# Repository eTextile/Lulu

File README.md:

# Lulu-MCU

**Programming light into textile**

Lulu is a hardware solution that interfaces between an LED light source, an optic fiber strand or bundle and soft circuit connections.
Providing an optic fiber connection toolset and workflow for E-Textiles and Wearable Technology applications.

### About The project
Lulu is providing a simple, reliable toolset for people who want to use side glow optical fibers in their eTextile and wearable projects.
Use of light in textile and fashion design is becoming more and more common and many schools started to teach this subject as a part of their textile design curriculum.
Optic fibers could be embedded in textiles as embroidery, in weaving, knitting and knotting process and many textile designs have been realized in recent years.
But often the designers lack the toolset for connecting the light sources with the embedded optic fibers, resulting in re-purposing bulky connectors and technology and hiding them behind the textiles.
Currently, each designer has to come up with their own re-purposed or DIY solution.
Lulu is a connector that optimizes the efficiency of the connection between the light source and the optical fibers to get a strong illumination.
Instead of struggling to solve the light source and connection problem, the designer can concentrate on the aesthetic and textile making process issues.

### Lulu branches
- **Lulu-star (master)**
  - This branch provide a tiny PCB with a 200mA LED, PWM driver and an optic fiber connector.
- **Lulu-daisy**
  - This branch provide a tiny PCB with an addressable LED (WS2812-mini, Dotstar, etc) and an optic fiber connector.
- **Lulu-MCU**
  - This branch provide a tiny PCB with a built in MCU (ATTiny10) that allow one-wire communication bus system.
- **Lulu**
  - This branch provide a motherboard (Lucette) that drive up to 16 Lulu that only contain a power LED and an optic fiber connector.

### Development tools & DOCs
 * **Web page**: [http://lulu.eTextile.org](http://lulu.eTextile.org "The project Web page")
 * **Kobakant web page**: [http://www.kobakant.at/KOBA/lulu-developments](http://www.kobakant.at/KOBA/lulu-developments "Kobakant project Web page")
 * **Repository**: [https://github.com/eTextile/Lulu/tree/master](https://github.com/eTextile/Lulu/tree/master "The project repository")
 * **License**: [CC-BY-SA](https://github.com/eTextile/Lulu/blob/master/LICENSE "See the Lulu license project")
 * **Video**: [Lulu project by Hannah](https://www.youtube.com/watch?v=drAoLd_eUWk "Lulu project Introduction")
 * **Video**: [Lulu project by Maurin](https://vimeo.com/249171264 "eTextile bus solution")
 * **Mail**: [lulu@etextile.org](mailto:lulu@etextile.org "eMail us")
 * **IRC**: [Riot](https://vector.im/develop/#/room/#lulu:matrix.org "Join us on the chat to collaborate in the development")
 * **Pictures**: [Flickr](https://www.flickr.com/groups/3908991@N25/ "Share your Lulu pictures project")

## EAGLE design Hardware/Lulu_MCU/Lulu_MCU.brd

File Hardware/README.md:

# Lulu-MCU / Hardware
**Programming light into textile**

# Lulu-MCU

## Hardware design
This branch of the Lulu project is using a 200mA power LED with current current circuitry.
As the project is focussing on embedded electronics we chosed an high power LED ; OSRAM OSLON SX seeking 200 mA/h 
Then it can be 5 hour of autonomy with a 1000 mA Lypo battery.
The LED is also providing a narrow angle (60°) this helps to focus the light in to the optic fiber wafer.
    See datasheet: https://github.com/eTextile/Lulu/blob/master/Hardware/DOCs/LY_CN5M.pdf
The brass tube connector have been selected to fit the outer diameter of the LED optics.
The PCB triangle shape have been selected to fit the zero waste production process.
All the components are SMD package to reduce the size and price of th PCB.
We have been experiencing a new way to hand solder the LED on the edge of the PCB but it is still not so handy.
Custom tooling will be designed and tested to help in that soldering process.

## Release notes
### Lulu-MCU 4.0.0
- Initial release (forked from Lulu-star 2.1.3)

## Lulu-MCU connecting
- [VCC] (+) 3.3 to 5 Voltes
- [GND] (-) GND
- [DATA] oneWire data bus

        +---+--------------+-------------------+-----
        |   |              |                   |
    + __|__ |              |                   |
    -  ___  |              |                   |
        |   |              |                   |
        +---|--------------|--+----------------|--+--
        |   |              |  |                |  |
        |   |            __|__|__            __|__|__
       _|___|_           \ +  - /            \ +  - /
      | +   - |           \    /              \    /
      |   M   |            \  /                \  /
      |   C   |             \/                  \/
      |   U   |              |                   |
      |       |--------------------- DATA ------------
      |_______|

## Lulu-MCU Powering
The Lulu-MCU board must be powered with a voltage betwin 3.3V to 5V.
DO NOT USE 3V single coin battery - voltage is too low and it will not work for long.
Prefer the use of rechargeable Lipo battery with small Lipo charger.
- https://www.powerstream.com/thin-primary-lithium.htm
- Charger technology
- Low discharge protection

## Lulu-MCU built-in LED driver
### Constant current source circuitry

**References**
- https://learn.adafruit.com/pixie-3-watt-smart-chainable-led-pixels/design
- http://www.instructables.com/id/Power-LED-s---simplest-light-with-constant-current/
- https://scienceprog.com/building-simple-constant-current-power-led-driver/
- http://www.pcbheaven.com/userpages/LED_driving_and_controlling_methods/?topic=worklog&p=3

### Circuit part list
| Designator                                      | MPN                       | Package                | Price per unit | Weblink                |
| ----------------------------------------------- | ------------------------- | -----------------------|--------------- |------------------------|
| Power LED / OSRAM 200mA                         | LY CN5M                   |                        | 0.65 $         | [LY-CN5M](https://fr.aliexpress.com/item/OSRAM-OSLON-SX-High-Power-LED-0-5W-3030-Yellow-LY-CN5M/32865040281.html?spm=a2g0s.9042311.0.0.27426c371XVtDl) |
| Q1 - large N-channel MOSFET                     | IRLML2060TRPBF            | SOT-23                 | 0,126 €        | [IRLML2060TRPBF](https://www.digikey.com/product-detail/en/infineon-technologies/IRLML2060TRPBF/IRLML2060TRPBFCT-ND/2271917) |
| T1 - small NPN transistor                       | MMBT2222A                 | SOT-23                 | 0,0412 €       | [MMBT2222A](https://www.digikey.com/product-detail/en/diodes-incorporated/MMBT2222A-7-F/MMBT2222A-FDICT-ND/815723) |
| R1 - 47k-ohm resistor                           | RT0603DRD0747KL           | 0603                   | 0,0147 €       | [R-47k-ohm ](https://www.digikey.com/product-detail/en/yageo/RT0603DRD0747KL/311-47KDCT-ND/1035828) |
| R2 - current set resistor - 2.7 ohms 1/4 watt   |                           | 1206                   | 0,0246 €       | [R-2.7-ohm](https://fr.farnell.com/walsin/wr12w2r70ftl/resist-couche-epaisse-2-7r-1-0/dp/2668305) |
| R3 - 10k pull-down resistor                     | RT0603DRD0710KL           | 0603                   | 0,     €       | [R-10k-ohm](https://www.digikey.com/product-detail/en/yageo/RT0603DRD0710KL/311-10KDCT-ND/1035680) |
| ATTiny10                                        |                           | SOT-                   | 0,     €       | [ATTiny10](...) |

**R2** is used to set the current limit and this doesn't depends on the voltage supply VDD.
**Q1** is used as a variable resistor. **Q1** starts out turned on by **R1**.
**T1** is used as an over-current sensing switch, and **R2** is the "sense resistor" that triggers **T1** when too much current is flowing.
The main current flow is through the LED's, through **Q1**, and through **R2**.
When too much current flows through **R2**, **T1** will start to turn on, which starts turning off **Q1**. Turning off **Q1** reduces the current through the LED's and **R2**.
So we've created a **feedback loop**, which continuously tracks the current and keeps it exactly at the set point at all times.
The NPN transistors **T1** have a specified 0.6V drop between base and emitter when on.
This means the voltage across their respective shunt resistors **R2** will always be 0.6V.
According to Ohm’s law, this means that the current through them will be '0.6 V / 2.7 Ohm', or about 222mA.

## PCB manufacturing characteristics
  - Base Material : FR-4 TG13
  - No. of Layers : 2 layers
  - PCB Thickness : 1 mm
  - PCB Color : Yelow
  - Surface Finish : HASL
  - Minimum Solder Mask Dam : 0.4 mm
  - Copper Weight : 1oz (35 µm)
    - For 300 mA we nead 0.15mm copper traces (https://www.4pcb.com/trace-width-calculator.html)
  - Minimum Drill Hole Size : 0.3 mm
  - Trace Width / Spacing : 5/5 mil
  - Blind or Buried Vias : NO
  - Plated Half-holes / Castellated Holes : YES
  - Impedance Control : NO

### Extra Part list
| Part                       | REF                      | Price per unit   | Weblink        |
| -------------------------- | ------------------------ | -----------------|--------------- |
| Brass tube                 | 2 mm Hole 5-10 mm Length |                  |                |
| JTE connector              | 1.5 / 8 mm               |                  |                |
| Optical fibres PMMA        | 0.25 mm x 35 pce         |                  |                |
| Optical fibres TPU         | 1.5, 2, 3 mm             |                  |                |
| Optical fibres tube + core |                          |                  | [www.leds-and-more.de](https://www.leds-and-more.de/catalog/15mm-lwl-lichtwellenleiter-lichtleiter-seitlich-leuchtend-p-1937.html?osCsid=2me5dl4q5amcvgb6tnbqfd87i5) |
| eTextile bus               |                          |                  |                |

## TODO
- [ ] Add ATTiny10 ont the KiCad desin
- [ ] Add POGO PINs on the PCB to flash the ATTiny10
- [ ] Change the PCB shape to put the tube angle to 90° from the e-Textile bus
- [ ] cool ref: https://hackaday.io/project/179554-tinyicoc

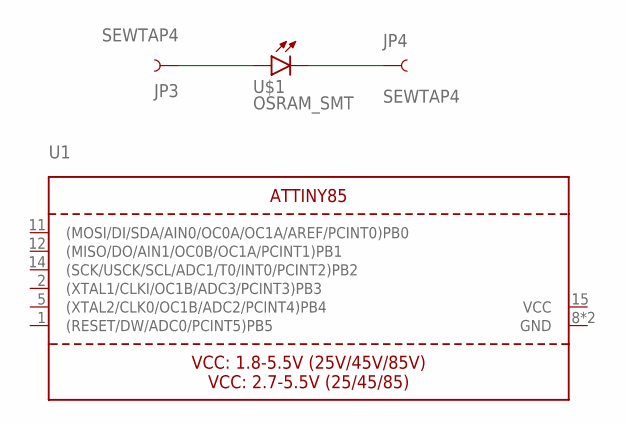
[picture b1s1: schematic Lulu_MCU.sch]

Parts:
JP3, JP4: SEWTAP4; PETAL-SMALL
U1: ATTINY85; MLF20_4X4MM_0.5MM_ATMEL
U$1: OSRAM_SMT; OSLON

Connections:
GND: U1.8 (GND), U1.THERMAL (GND)
unnamed: JP3.1, U$1.A
unnamed: JP4.1, U$1.C
VCC: U1.15 (VCC)

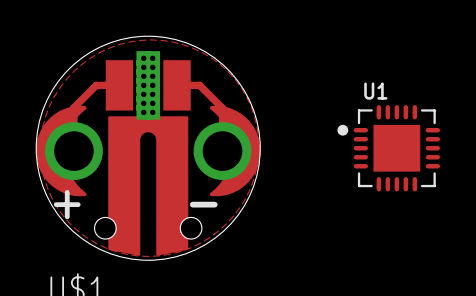
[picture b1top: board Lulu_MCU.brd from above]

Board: 2 copper layers, 12.4 x 12.4 mm, 4 parts (0 on the bottom side), 3 nets.

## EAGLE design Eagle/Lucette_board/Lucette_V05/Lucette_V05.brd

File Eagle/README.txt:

#Eagle

## Project content
 - Lucette Eagle PCB
 - Lulu Eagle PCB

See the README inside the project content files

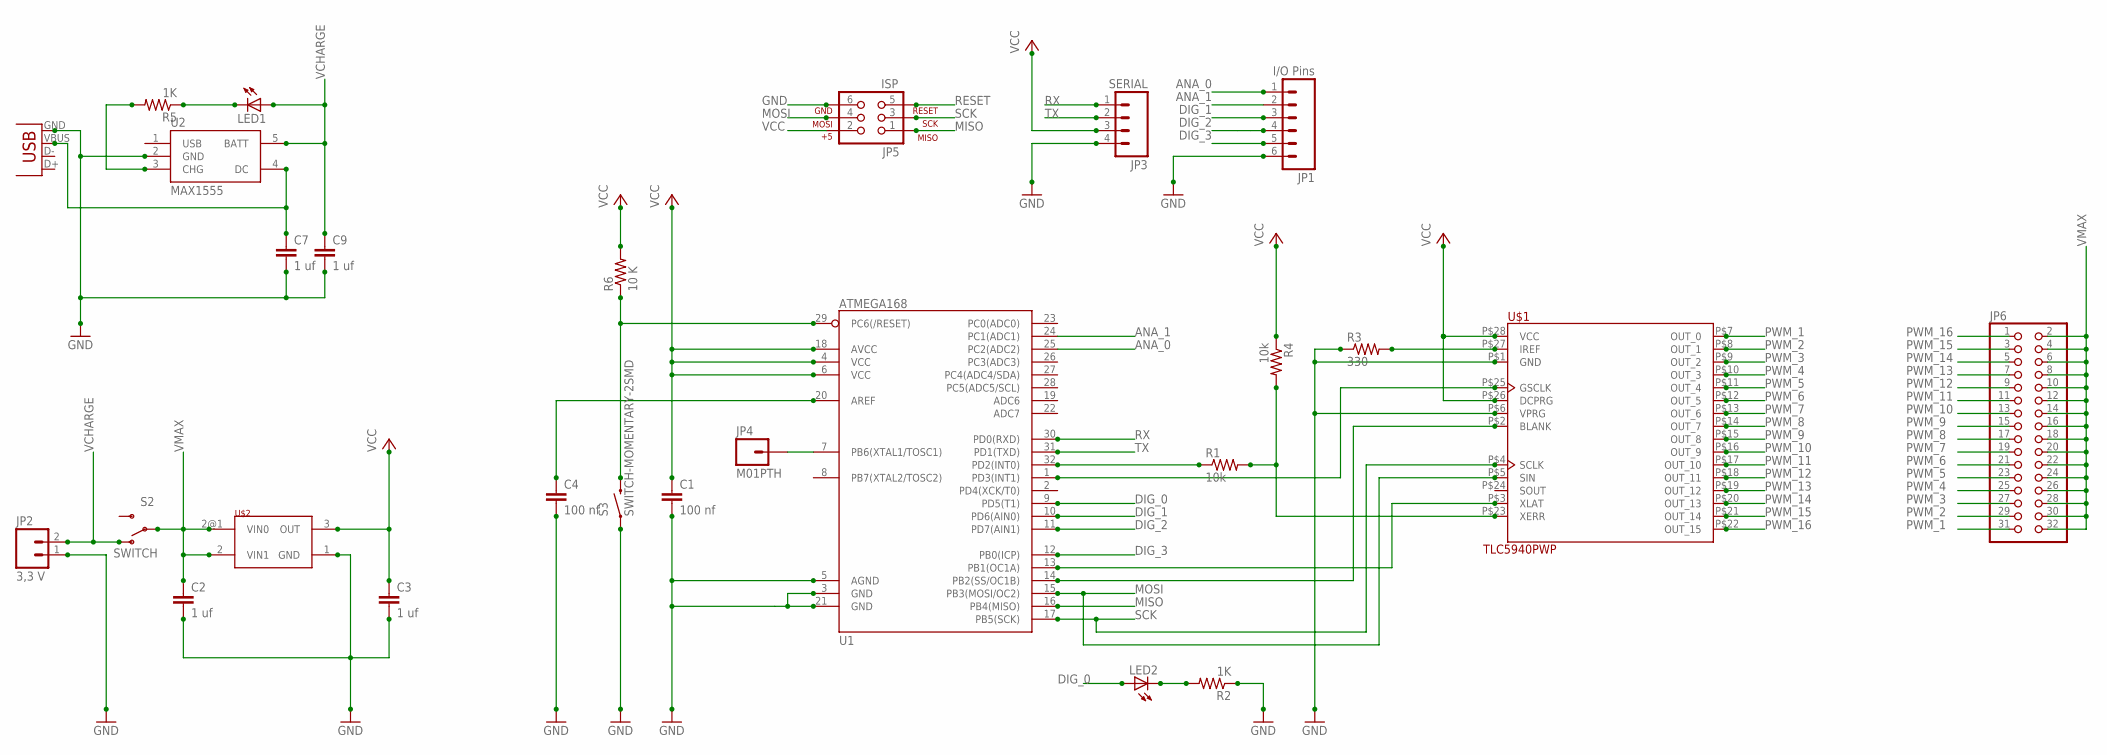
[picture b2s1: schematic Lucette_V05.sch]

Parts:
C1, C4: 100 nf; 0805
C2, C3, C7, C9: 1 uf; 0805
JP1: I/O Pins; 1X06-SMD
JP2: 3,3 V; S2B-PH
JP3: SERIAL; 1X04-SMD
JP4: M01PTH; 1X01
JP5: ISP; 2X3
JP6: PINHD-2X16/90; 2X16/90
LED1, LED2: LEDCHIP-LED0805; CHIP-LED0805
R1, R4: 10k; 1206
R2, R5: 1K; 1206
R3: 330; 1206
R6: 10 K; 1206
S2: SWITCH; AYZ0202
S3: SWITCH-MOMENTARY-2SMD; TACTILE_SWITCH_SMD
U1: ATMEGA168; TQFP32-08
U2: MAX1555; SOT23-5
U$1: TLC5940PWP; PWP-28
U$2: MCP1703; SOT98
X1: USBOLD; USB-MINIB-OLD

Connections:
ANA_0: JP1.1, U1.25 (PC2(ADC2))
ANA_1: JP1.2, U1.24 (PC1(ADC1))
DIG_0: LED2.A, U1.9 (PD5(T1))
DIG_1: JP1.3, U1.10 (PD6(AIN0))
DIG_2: JP1.4, U1.11 (PD7(AIN1))
DIG_3: JP1.5, U1.12 (PB0(ICP))
GND: C1.2, C2.2, C3.2, C4.2, C7.2, C9.2, JP1.6, JP2.1, JP3.4, JP5.6, R2.1, R3.1, S3.1, U1.3 (GND), U1.5 (AGND), U1.21 (GND), U2.2 (GND), U$1.P$1 (GND), U$1.P$6 (VPRG), U$2.1 (GND), X1.GND
MISO: JP5.1, U1.16 (PB4(MISO))
MOSI: JP5.4, U1.15 (PB3(MOSI/OC2)), U$1.P$5 (SIN)
unnamed: R1.2, R4.2, U$1.P$23 (XERR)
unnamed: R1.1, U1.32 (PD2(INT0))
unnamed: C7.1, U2.4 (DC), X1.VBUS
unnamed: R5.2, U2.3 (CHG)
unnamed: U1.13 (PB1(OC1A)), U$1.P$3 (XLAT)
unnamed: LED1.C, R5.1
unnamed: C4.1, U1.20 (AREF)
unnamed: R3.2, U$1.P$27 (IREF)
unnamed: JP4.1, U1.7 (PB6(XTAL1/TOSC1))
unnamed: LED2.C, R2.2
unnamed: U1.1 (PD3(INT1)), U$1.P$25 (GSCLK)
unnamed: U1.14 (PB2(SS/OC1B)), U$1.P$2 (BLANK)
PWM_1: JP6.31, U$1.P$7 (OUT_0)
PWM_2: JP6.29, U$1.P$8 (OUT_1)
PWM_3: JP6.27, U$1.P$9 (OUT_2)
PWM_4: JP6.25, U$1.P$10 (OUT_3)
PWM_5: JP6.23, U$1.P$11 (OUT_4)
PWM_6: JP6.21, U$1.P$12 (OUT_5)
PWM_7: JP6.19, U$1.P$13 (OUT_6)
PWM_8: JP6.17, U$1.P$14 (OUT_7)
PWM_9: JP6.15, U$1.P$15 (OUT_8)
PWM_10: JP6.13, U$1.P$16 (OUT_9)
PWM_11: JP6.11, U$1.P$17 (OUT_10)
PWM_12: JP6.9, U$1.P$18 (OUT_11)
PWM_13: JP6.7, U$1.P$19 (OUT_12)
PWM_14: JP6.5, U$1.P$20 (OUT_13)
PWM_15: JP6.3, U$1.P$21 (OUT_14)
PWM_16: JP6.1, U$1.P$22 (OUT_15)
RESET: JP5.5, R6.1, S3.3 (2), U1.29 (PC6(/RESET))
RX: JP3.1, U1.30 (PD0(RXD))
SCK: JP5.3, U1.17 (PB5(SCK)), U$1.P$4 (SCLK)
TX: JP3.2, U1.31 (PD1(TXD))
VCC: C1.1, C3.1, JP3.3, JP5.2, R4.1, R6.2, U1.4 (VCC), U1.6 (VCC), U1.18 (AVCC), U$1.P$26 (DCPRG), U$1.P$28 (VCC), U$2.3 (OUT)
VCHARGE: C9.1, JP2.2, LED1.A, S2.1 (O), U2.5 (BATT)
VMAX: C2.1, JP6.2, JP6.4, JP6.6, JP6.8, JP6.10, JP6.12, JP6.14, JP6.16, JP6.18, JP6.20, JP6.22, JP6.24, JP6.26, JP6.28, JP6.30, JP6.32, S2.2, U$2.2 (VIN1), U$2.2@1 (VIN0)

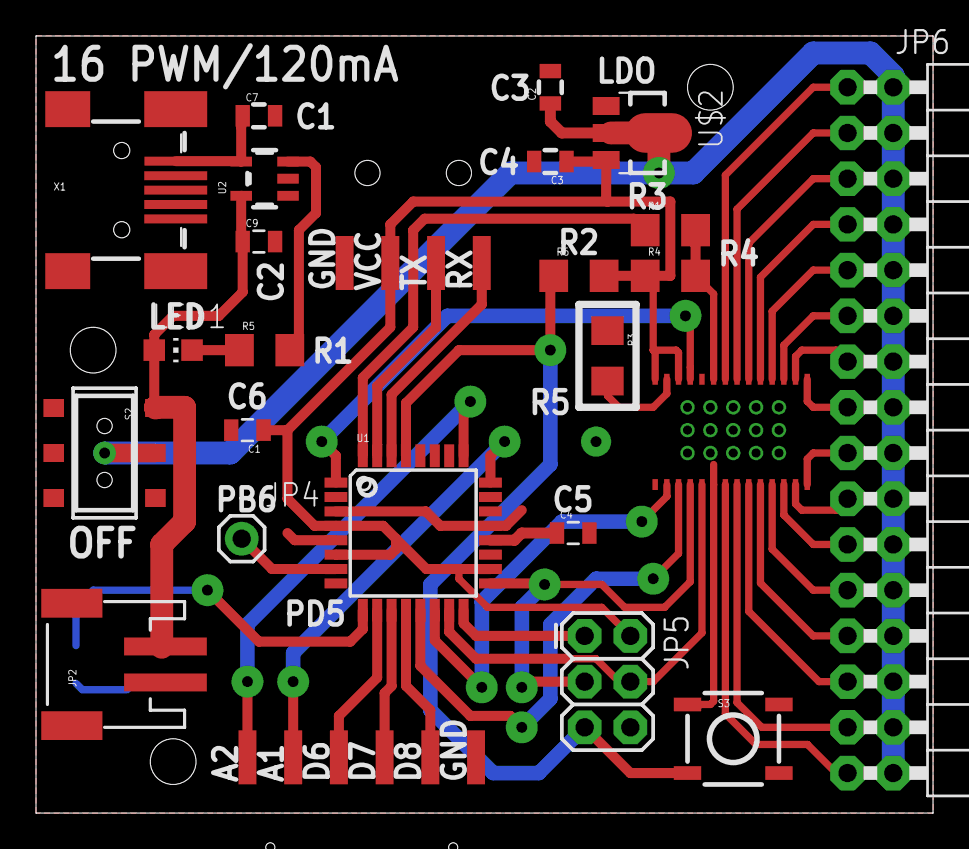
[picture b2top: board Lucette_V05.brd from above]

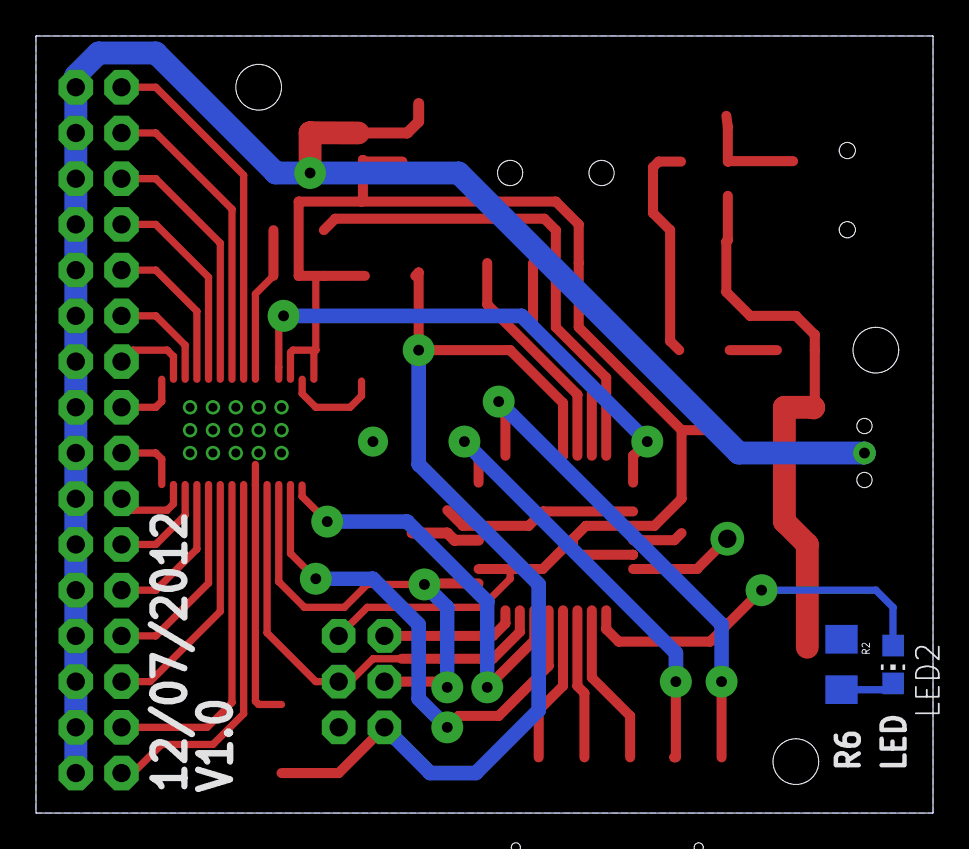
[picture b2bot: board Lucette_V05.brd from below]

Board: 2 copper layers, 49.8 x 43.2 mm, 27 parts (2 on the bottom side), 44 nets.

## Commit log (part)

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2014-05-06 Update lucette_seq.ino
    Optimisation du protocole de communication entre la carte Lucette et un logiciel Pilote réalisé avec PureData. Pour contrôler une sortie de la carte Lucette il faut utiliser trois octets :
    le premier pour définir la LED à actualiser le second et le troisième pour définir la valeur 12 bits (0-4095) qui correspond à l'intensité de la LED.
2014-05-06 Update README.md
    Fonctions de la carte Lucette / fork du projet Arduino
2014-05-07 Update README.md
    cleaning
2014-05-07 Create LEDs_seq
2014-05-07 Create Seq_master
2014-05-07 Rename LEDs_seq to set_seq
2014-05-10 Update Seq_master
    bug fix
2014-05-17 Update Lucette_seq.ino
    Bug fix in ledUpdate();
2014-05-21 Update Lucette_seq.ino
    adding new parcing methode, readBytesUntil();
2014-05-22 Update Lucette_seq.ino
    Bug fix
2014-06-04 Update Lucette_seq.ino
    Bug fix.
    Add new communication
2014-06-06 Update Seq_master
    New new!
2014-06-29 Rename Seq_master to Seq_master.pd
2014-06-29 Rename set_seq to set_seq.pd
2014-06-29 Rename set_seq.pd to led_seq.pd
2014-07-01 Update Lucette_seq.ino
    add ERROR Handling if a LED is diconnected.
2015-10-08 added eagle boards
2016-10-13 clean up
2016-10-20 clean README
2016-10-20 add Lulu PCB
2016-10-20 re-organised README
2016-10-20 clean formating
2016-10-20 clear formatting
2016-11-04 Added tutorial link
2017-01-15 Fixed URL link
2017-12-13 Suppressed pictures
2017-12-13 Added pictures
2017-12-13 minor changes
2017-12-13 Added local pictures
2017-12-13 Initial commit from Lucette branche
2017-12-13 Removed PureData Driver
2018-01-10 Added test code for ATTiny10
2018-01-12 Added TPI programmer info...
2018-01-31 Adeed 1-wire github project ref
2018-02-04 Renamed foldes
2018-02-05 Added project overview & social media links
2018-02-05 Moved text from master readMe to folder readMe
2018-02-05 Less is more
2018-02-05 Markdown syntax cleanUp
2018-02-05 Mismatch with hard and soft
2018-02-05 Added picture
2018-02-05 Added link of original work
2018-02-05 Added protocol explanation
2018-02-05 Removed ATTiny10 test files
2018-02-05 Added initial firmware forked from Kevin Cuzner
2018-02-05 Updated introduction
2018-02-05 Removed pictures and old files
2018-02-05 Added TODO list
2018-02-05 Added ATTiny10 datasheet
2018-02-05 Removed hided file
2018-02-06 Added eMail & videos links
2018-02-06 play with Markdown
2018-02-09 Added all Branch to the README
2018-02-26 Added comments
2018-02-26 Updated webpage URL
2018-02-26 Added web link of 1-wire lib for teensy
2018-02-26 Added array for part list
2018-02-26 Added description
2018-02-26 Updated TODO list
2018-02-26 Updated pull-up resistor value
2018-02-27 Added Markdown liste select
2018-02-27 Added price per unit
2018-03-18 Added new web page link
2018-03-18 Added OpenJSCAD submodule
2018-03-18 Removed OpenJSCAD
2018-03-18 Added OpenJSCAD-web
2018-03-18 Playing with webPage
2018-03-18 Removed TODO
2018-03-19 Added kobakant webpage
2018-04-01 syntax errors
2018-05-02 Removed CNAME
2018-05-02 Added Bootstrap web page
2018-05-07 Removed credit & added new picture
2018-05-07 Added .gitignore
2018-05-08 Minor change
2018-05-09 Updated Branches name
2018-05-09 Updated Upverter web link
2018-05-09 Removed MCU files
2018-05-09 Updated README with new diagram
2018-05-09 Added warning
2018-05-09 Updatad schematics for daisy-chained
2018-05-10 Added Lulu-daisy branche
2018-05-11 Added schematic drawing
2018-05-11 Removed Software file
2018-05-11 Removed .gitmodules
2018-05-12 Removed unused file
2018-05-12 Update branches
2018-05-13 Added 3D openscad
2018-05-14 Updated measurements
2018-05-15 Updated branch list
2018-05-15 Removed unused files
2018-05-15 Removed unused folder
2018-05-15 Updated title
2018-05-18 is back
2018-05-18 footprint_connection.jpg
2018-05-18 Added footprint_connection.jpg
2018-05-20 Added footprint connection picture
2018-05-21 Updated Part list
2018-05-21 Updated Project content
2018-05-28 Small fix
2018-06-03 Added driver circut picture
2018-06-04 Added connector
2018-06-04 Added link to new PCB design
2018-06-11 Added more explanations
2018-06-11 Added datasheet
2018-06-12 Updatad part list
2018-06-12 Removed resistor value R1
2018-06-26 added PCB specs
2018-06-26 Added GERBER files
2018-08-03 Added LED Weblink
2018-08-21 Added new LED datasheet
2018-08-21 Removed unused LED datasheet
2018-08-21 Added KiCad file
2018-08-21 Added file naming conventions
2018-08-21 Renamed folder
2018-08-21 Removed - kicad bad config
2018-08-21 Fixed weblink
2018-08-21 Added circuit part list weblinks
2018-08-30 PCB in progress
2018-08-30 Added e-textile bus datasheet
2018-08-30 Added PCB shape path
2018-08-30 Removed openScad 3D file -> 3D is now done with KiCad
2018-08-31 Renamed file
2018-08-31 TODO: Add this file to the .gitignore
2018-08-31 .gitignore file
2018-09-02 Added brass tube pad footprint
2018-09-02 Updated Lulu 212 path
2018-09-02 Added file
2018-09-03 Added new file for 2D-3D components
2018-09-03 Moved file to Hardware/kicad_Lulu_star/Lulu_star_212/Library/
2018-09-03 Added PCB pin fonctions top & bottom
2018-09-04 Added some info for trace width calculation
2018-09-04 Routing done
2018-09-04 Fixed 3D XYZ pos for KiCad import
2018-09-05 Updated pictures size
2018-09-06 Added Pull down resistor on PWM pin
2018-09-12 Correct the thermal pad GND connection
2018-09-14 Updated ground plane
2018-09-18 Move down all components of the PCB
2018-09-21 Added ziped GERBER files for production
2018-09-21 Updated clearance to 0.2
2018-09-21 Added Software folder for Arduino examples
2018-09-22 Start
2018-09-22 Updated library path with relative position
2018-10-09 test
2018-10-24 Added new Arduino examples
2018-10-25 Added - Branche naming conventions
2018-10-25 Added releases info
2018-10-25 Added README to list the the Arduino examples
2018-10-26 Added bigger path
2018-11-07 Updated syntax
2018-11-19 Added Updated Lulu_star_213
2018-11-19 Removed Lulu_star_212
2018-11-19 In production
2018-11-19 Added BOM
2018-11-19 Updated BOM
2018-11-19 Updated Release notes for V2.1.3
2018-11-23 Updated schematics & picture
2018-11-23 CleanUp syntax
2018-11-23 Updated picture
2019-01-08 adding lulu daisy to the master branch
2019-01-17 Updatad exemples
2019-01-17 Removed .DS_Store
2019-01-17 Removed Lulu-daisy txt
2019-01-17 Added design specs
2019-01-17 Removed TODO list
2019-01-17 Added new design
2019-01-17 Removed unused docs
2019-01-17 Added library Weblink
2019-01-18 Update Lulu-star picture
2019-01-18 Added Lulu-star picture to the carousel
2019-01-31 Updated TODO list
2019-01-31 added .txt extension
2019-01-31 mv Software>Firmware
2019-01-31 Added Arduino compatibility
2019-01-31 Added new docs
2019-01-31 Updatad
2019-01-31 Forked from Lulu-star
2019-01-31 Updated TPI ASCii
2019-02-01 CleanUP
2019-02-01 New picture
2019-02-04 Working prototype
2019-02-04 Set LED to 200mA
2019-02-04 Added Lulu_ID & Lulu_value to the oneWire bus comm
2019-02-05 Added BRODCAST ID
2019-02-07 Added top level communication protocol. attempt to configure the hardware on the fly to handle 16 bit Hardware PWM & 1-Wire Hardware decoder
2019-02-07 Added DOCs
2019-02-08 Merged 1-Wire & embedded LED fading pattern generator
2019-02-11 added non blocking delay & correct some bugs. Working as a charme
2019-02-11 Improved LEDs control sync
2019-02-25 swatch demo code
2019-02-26 Routing in process
2019-02-26 Moved fies
2019-02-26 Updated for security
2019-03-19 Updated Kobakant/lulu project URL
2019-03-19 Moved Lulu_daisySwatch.ino to the Lulu-daisy branch
2019-03-19 Added Lulu_daisySwatch.ino
2019-04-12 testing
2019-04-15 Updated hardware design explanation
2019-04-15 Under testing
2019-04-15 Under routing
2019-04-15 Routing
2019-04-15 Added doc
2019-04-15 Updatad .pdf
2019-04-15 back in time
2019-04-15 Added .odp (libre office) source file
2019-04-18 Added Picture of the 1-wire bus with ATTiny-10
2019-11-14 Updatad picture
2019-11-14 Updated title typo
2019-11-14 Bump mixin-deep from 1.3.1 to 1.3.2 in /docs
    Bumps [mixin-deep](https://github.com/jonschlinkert/mixin-deep) from 1.3.1 to 1.3.2.
    - [Release notes](https://github.com/jonschlinkert/mixin-deep/releases)
    - [Commits](https://github.com/jonschlinkert/mixin-deep/compare/1.3.1...1.3.2)
2019-11-14 Bump lodash.mergewith from 4.6.1 to 4.6.2 in /docs
    Bumps [lodash.mergewith](https://github.com/lodash/lodash) from 4.6.1 to 4.6.2.
    - [Release notes](https://github.com/lodash/lodash/releases)
    - [Commits](https://github.com/lodash/lodash/commits)
2019-11-14 Bump fstream from 1.0.11 to 1.0.12 in /docs
    Bumps [fstream](https://github.com/npm/fstream) from 1.0.11 to 1.0.12.
    - [Release notes](https://github.com/npm/fstream/releases)
    - [Commits](https://github.com/npm/fstream/compare/v1.0.11...v1.0.12)
2019-11-14 Bump handlebars from 4.0.12 to 4.5.2 in /docs
    Bumps [handlebars](https://github.com/wycats/handlebars.js) from 4.0.12 to 4.5.2.
    - [Release notes](https://github.com/wycats/handlebars.js/releases)
    - [Changelog](https://github.com/wycats/handlebars.js/blob/master/release-notes.md)
    - [Commits](https://github.com/wycats/handlebars.js/compare/v4.0.12...v4.5.2)
2019-11-14 Added favicon
2019-11-17 Update typos
2019-11-18 Bump jquery from 3.3.1 to 3.4.0 in /docs
    Bumps [jquery](https://github.com/jquery/jquery) from 3.3.1 to 3.4.0.
    - [Release notes](https://github.com/jquery/jquery/releases)
    - [Commits](https://github.com/jquery/jquery/compare/3.3.1...3.4.0)
2019-11-18 Bump js-yaml from 3.12.1 to 3.13.1 in /docs
    Bumps [js-yaml](https://github.com/nodeca/js-yaml) from 3.12.1 to 3.13.1.
    - [Release notes](https://github.com/nodeca/js-yaml/releases)
    - [Changelog](https://github.com/nodeca/js-yaml/blob/master/CHANGELOG.md)
    - [Commits](https://github.com/nodeca/js-yaml/compare/3.12.1...3.13.1)
2019-11-18 Bump eslint-utils from 1.3.1 to 1.4.3 in /docs
    Bumps [eslint-utils](https://github.com/mysticatea/eslint-utils) from 1.3.1 to 1.4.3.
    - [Release notes](https://github.com/mysticatea/eslint-utils/releases)
    - [Commits](https://github.com/mysticatea/eslint-utils/compare/v1.3.1...v1.4.3)
2019-11-18 Testing button
2019-11-18 Updated button
2019-12-08 Renamed github link
2019-12-12 Berlin
2020-03-14 Bump acorn from 6.0.7 to 6.4.1 in /docs
    Bumps [acorn](https://github.com/acornjs/acorn) from 6.0.7 to 6.4.1.
    - [Release notes](https://github.com/acornjs/acorn/releases)
    - [Commits](https://github.com/acornjs/acorn/compare/6.0.7...6.4.1)
2020-04-16 Bump https-proxy-agent from 2.2.1 to 2.2.4 in /docs
    Bumps [https-proxy-agent](https://github.com/TooTallNate/node-https-proxy-agent) from 2.2.1 to 2.2.4.
    - [Release notes](https://github.com/TooTallNate/node-https-proxy-agent/releases)
    - [Commits](https://github.com/TooTallNate/node-https-proxy-agent/compare/2.2.1...2.2.4)
2020-04-29 Bump jquery from 3.4.0 to 3.5.0 in /docs
    Bumps [jquery](https://github.com/jquery/jquery) from 3.4.0 to 3.5.0.
    - [Release notes](https://github.com/jquery/jquery/releases)
    - [Commits](https://github.com/jquery/jquery/compare/3.4.0...3.5.0)
2020-09-04 Bump node-sass from 4.11.0 to 4.13.1 in /docs
    Bumps [node-sass](https://github.com/sass/node-sass) from 4.11.0 to 4.13.1.
    - [Release notes](https://github.com/sass/node-sass/releases)
    - [Changelog](https://github.com/sass/node-sass/blob/master/CHANGELOG.md)
    - [Commits](https://github.com/sass/node-sass/compare/v4.11.0...v4.13.1)
2020-09-06 Bump handlebars from 4.5.2 to 4.7.6 in /docs
    Bumps [handlebars](https://github.com/wycats/handlebars.js) from 4.5.2 to 4.7.6.
    - [Release notes](https://github.com/wycats/handlebars.js/releases)
    - [Changelog](https://github.com/handlebars-lang/handlebars.js/blob/master/release-notes.md)
    - [Commits](https://github.com/wycats/handlebars.js/compare/v4.5.2...v4.7.6)
2020-10-09 Added https
2020-10-09 dirty commit
2021-01-29 Updated form link that was off

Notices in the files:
parts and their libraries:
LilyPad-Wearables: Licensing:Creative Commons ShareAlike 4.0 International - https://creativecommons.org/licenses/by-sa/4.0
microbuilder: This work is placed in the public domain, and may be freely used for commercial and non-commercial work with the following conditions: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
